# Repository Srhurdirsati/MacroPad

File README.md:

# MacroPad
This is a small **4-key RGB macro pad** project built using the Seeed Studio XIAO RP2040.  
It is designed as a beginner-friendly hardware + firmware project and can be used as a USB macro pad for shortcuts, media control, or productivity.

---

##  Features

- 4 mechanical keys
- Per-key RGB lighting using SK6812 MINI LEDs
- Rotary encoder for volume / Brightness
- OLED display for status 
- USB HID 
- Compact custom PCB
- Customizable Code For Customized Features

---

## Components Used

### Microcontroller
- **Seeed Studio XIAO RP2040**  
  Link: https://robu.in/product/seeed-studio-xiao-rp2040-v1-0/ $6 With Shipping

### Mechanical Switches
- **Cherry MX 5-pin switches (Silent Red)**  
  Link:  
  https://www.thecosmicbyte.com/product/cherry-mx-mechancial-5-pin-switches-compatible-with-hot-swappable-keyboards-pack-of-10/?attribute_pa_switch-type=mx-silent-red&utm_source=Bing%20Shopping&utm_campaign=Bingfeeds&utm_medium=cpc&utm_term=78989 $6 With Shipping 

### Other Parts
- SK6812 RGB LEDs (5 pcs) $1 From My Local Shop 
- Rotary encoder wih switch  $2 from my local shop 
- [0.96" I2C OLED display](https://robu.in/product/0-96-oled-display-module/) - $3 with shipping  
- Custom PCB (JLCPCB – approx **$11 USD** for prototype with shiping )

   GRAND TOTAL = 6+6+1+2+3+11 = 39 => ~$40

---

## How To Use Rorary Encoder 

- Double Click to switch btw brightness and volume
- Scroll to adjust
- Tripple Click To Switch RGB Modes
- Single Click For Play Pause

   CODE CAN BE EDITED AS PER CHOICE   

---

## Images

## JLC Cart

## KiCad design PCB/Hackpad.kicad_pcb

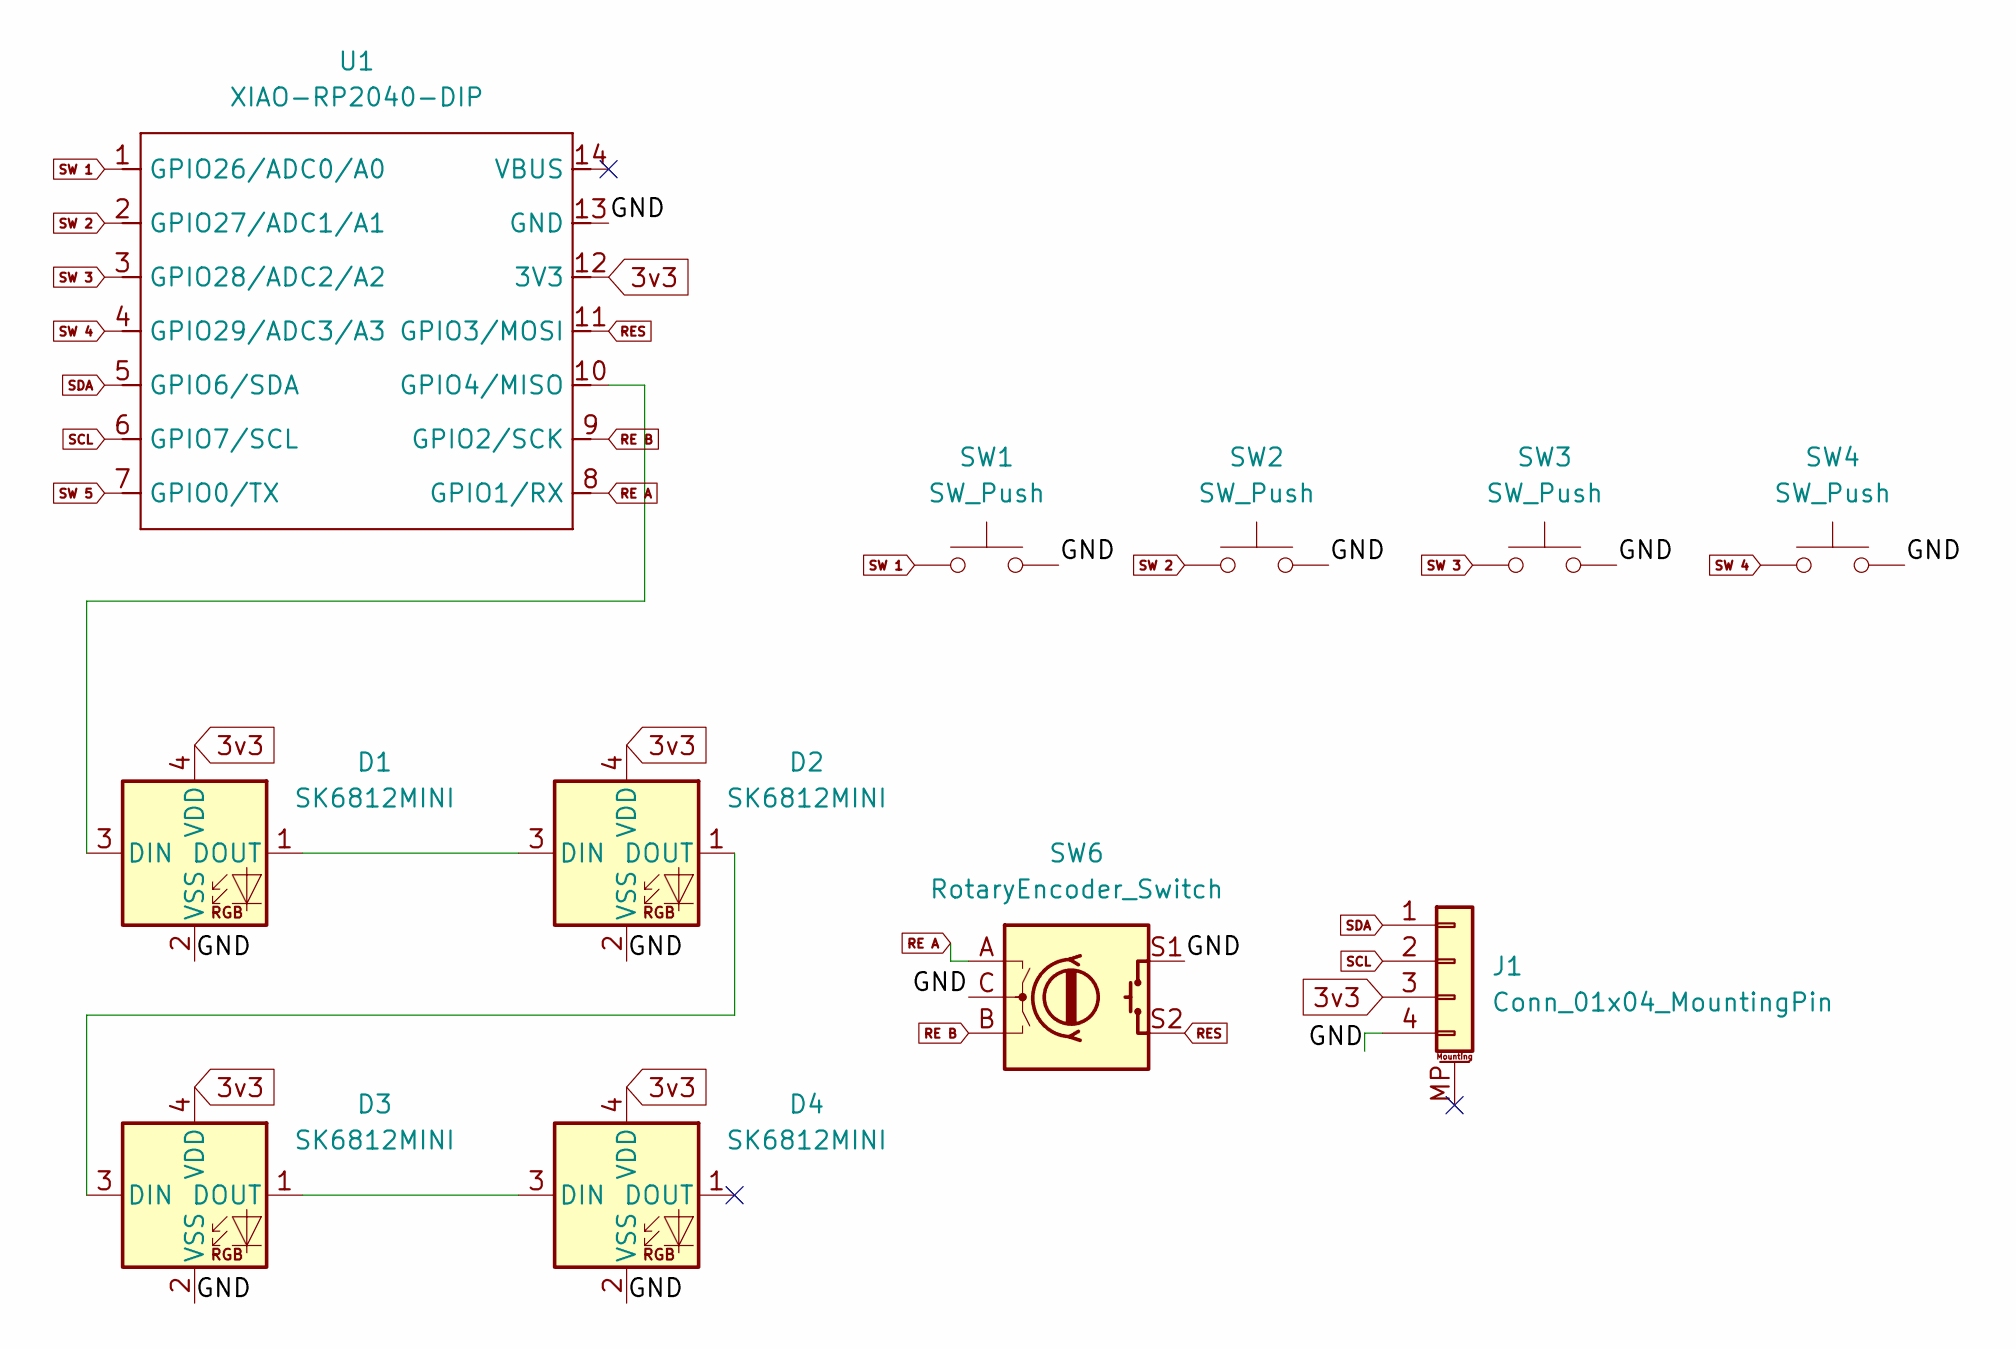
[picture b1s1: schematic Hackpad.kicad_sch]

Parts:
D1, D2, D3, D4: SK6812MINI; LED_SK6812MINI_PLCC4_3.5x3.5mm_P1.75mm
J1: Conn_01x04_MountingPin; PinHeader_1x04_P1.00mm_Vertical
SW1, SW2, SW3, SW4: SW_Push; SW_Cherry_MX_1.00u_PCB
SW6: RotaryEncoder_Switch; RotaryEncoder_Alps_EC11E-Switch_Vertical_H20mm
U1: XIAO-RP2040-DIP

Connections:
3v3: D1.4 (VDD), D2.4 (VDD), D3.4 (VDD), D4.4 (VDD), J1.3, U1.12 (3V3)
/GND: D1.2 (VSS), D2.2 (VSS), D3.2 (VSS), D4.2 (VSS), J1.4, SW1.2, SW2.2, SW3.2, SW4.2, SW6.C, SW6.S1, U1.13 (GND)
unnamed: D1.3 (DIN), U1.10 (GPIO4/MISO)
unnamed: D1.1 (DOUT), D2.3 (DIN)
unnamed: D2.1 (DOUT), D3.3 (DIN)
unnamed: D3.1 (DOUT), D4.3 (DIN)
RE A: SW6.A, U1.8 (GPIO1/RX)
RE B: SW6.B, U1.9 (GPIO2/SCK)
RES: SW6.S2, U1.11 (GPIO3/MOSI)
SCL: J1.2, U1.6 (GPIO7/SCL)
SDA: J1.1, U1.5 (GPIO6/SDA)
SW 1: SW1.1, U1.1 (GPIO26/ADC0/A0)
SW 2: SW2.1, U1.2 (GPIO27/ADC1/A1)
SW 3: SW3.1, U1.3 (GPIO28/ADC2/A2)
SW 4: SW4.1, U1.4 (GPIO29/ADC3/A3)
SW 5: U1.7 (GPIO0/TX)

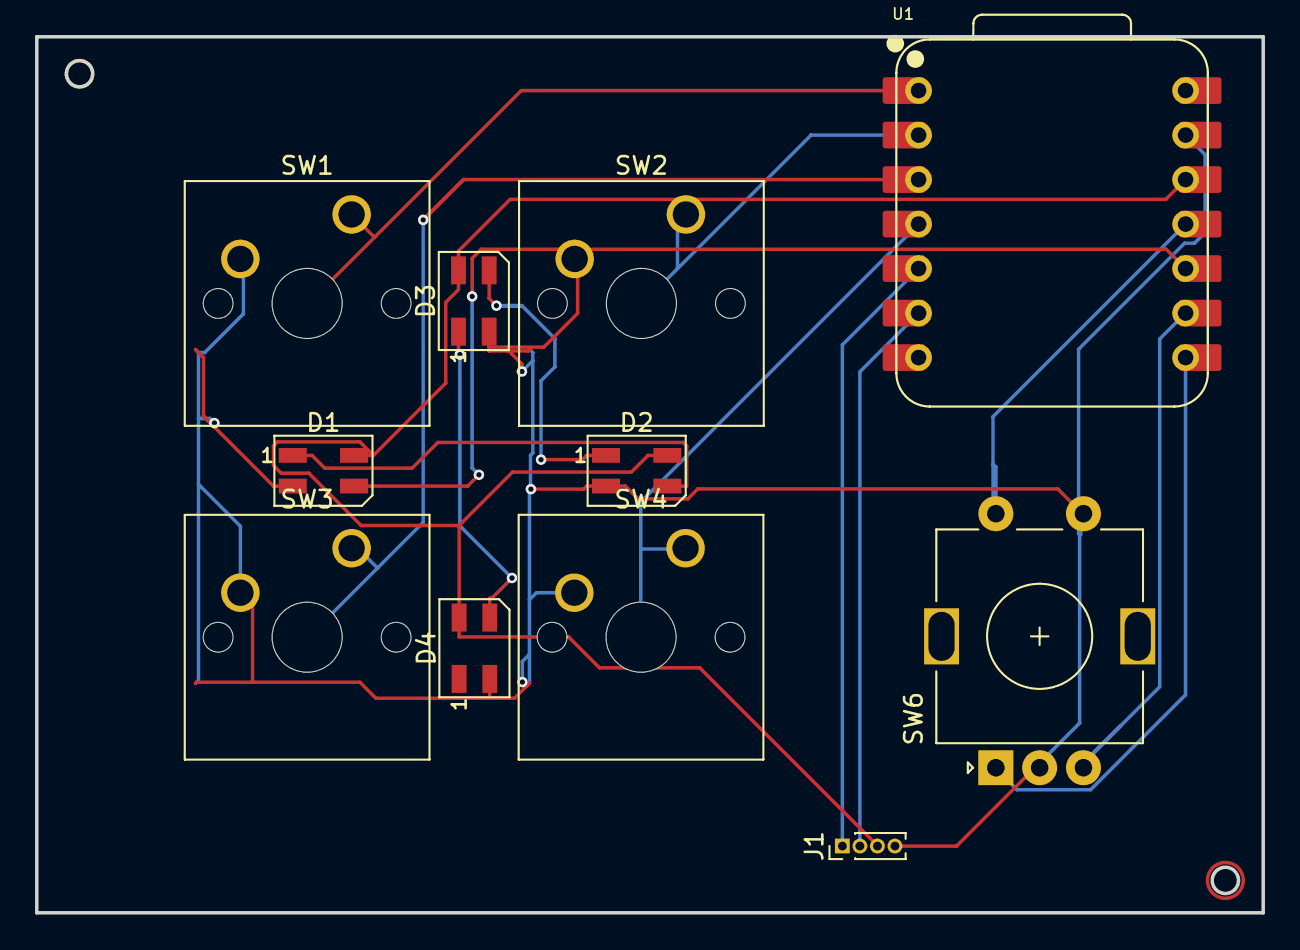
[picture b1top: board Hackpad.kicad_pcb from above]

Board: 2 copper layers, 70.0 x 50.0 mm, 11 parts (0 on the bottom side), 15 nets.

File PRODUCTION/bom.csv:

Designator,Footprint,Quantity,Value,LCSC Part #
"D1, D2, D3, D4",LED_SK6812MINI_PLCC4_3.5x3.5mm_P1.75mm,4,SK6812MINI,
J1,PinHeader_1x04_P1.00mm_Vertical,1,Conn_01x04_MountingPin,
"SW1, SW2, SW3, SW4",SW_Cherry_MX_1.00u_PCB,4,SW_Push,
SW6,RotaryEncoder_Alps_EC11E-Switch_Vertical_H20mm,1,RotaryEncoder_Switch,
U1,XIAO-RP2040-DIP,1,XIAO-RP2040-DIP,

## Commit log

2025-12-18 Fix pricing and links in README.md
    Updated pricing details and corrected links in the README.
2025-12-18 Add firmware for RGB and volume control
    Initial implementation of firmware with RGB control and volume adjustment features.
